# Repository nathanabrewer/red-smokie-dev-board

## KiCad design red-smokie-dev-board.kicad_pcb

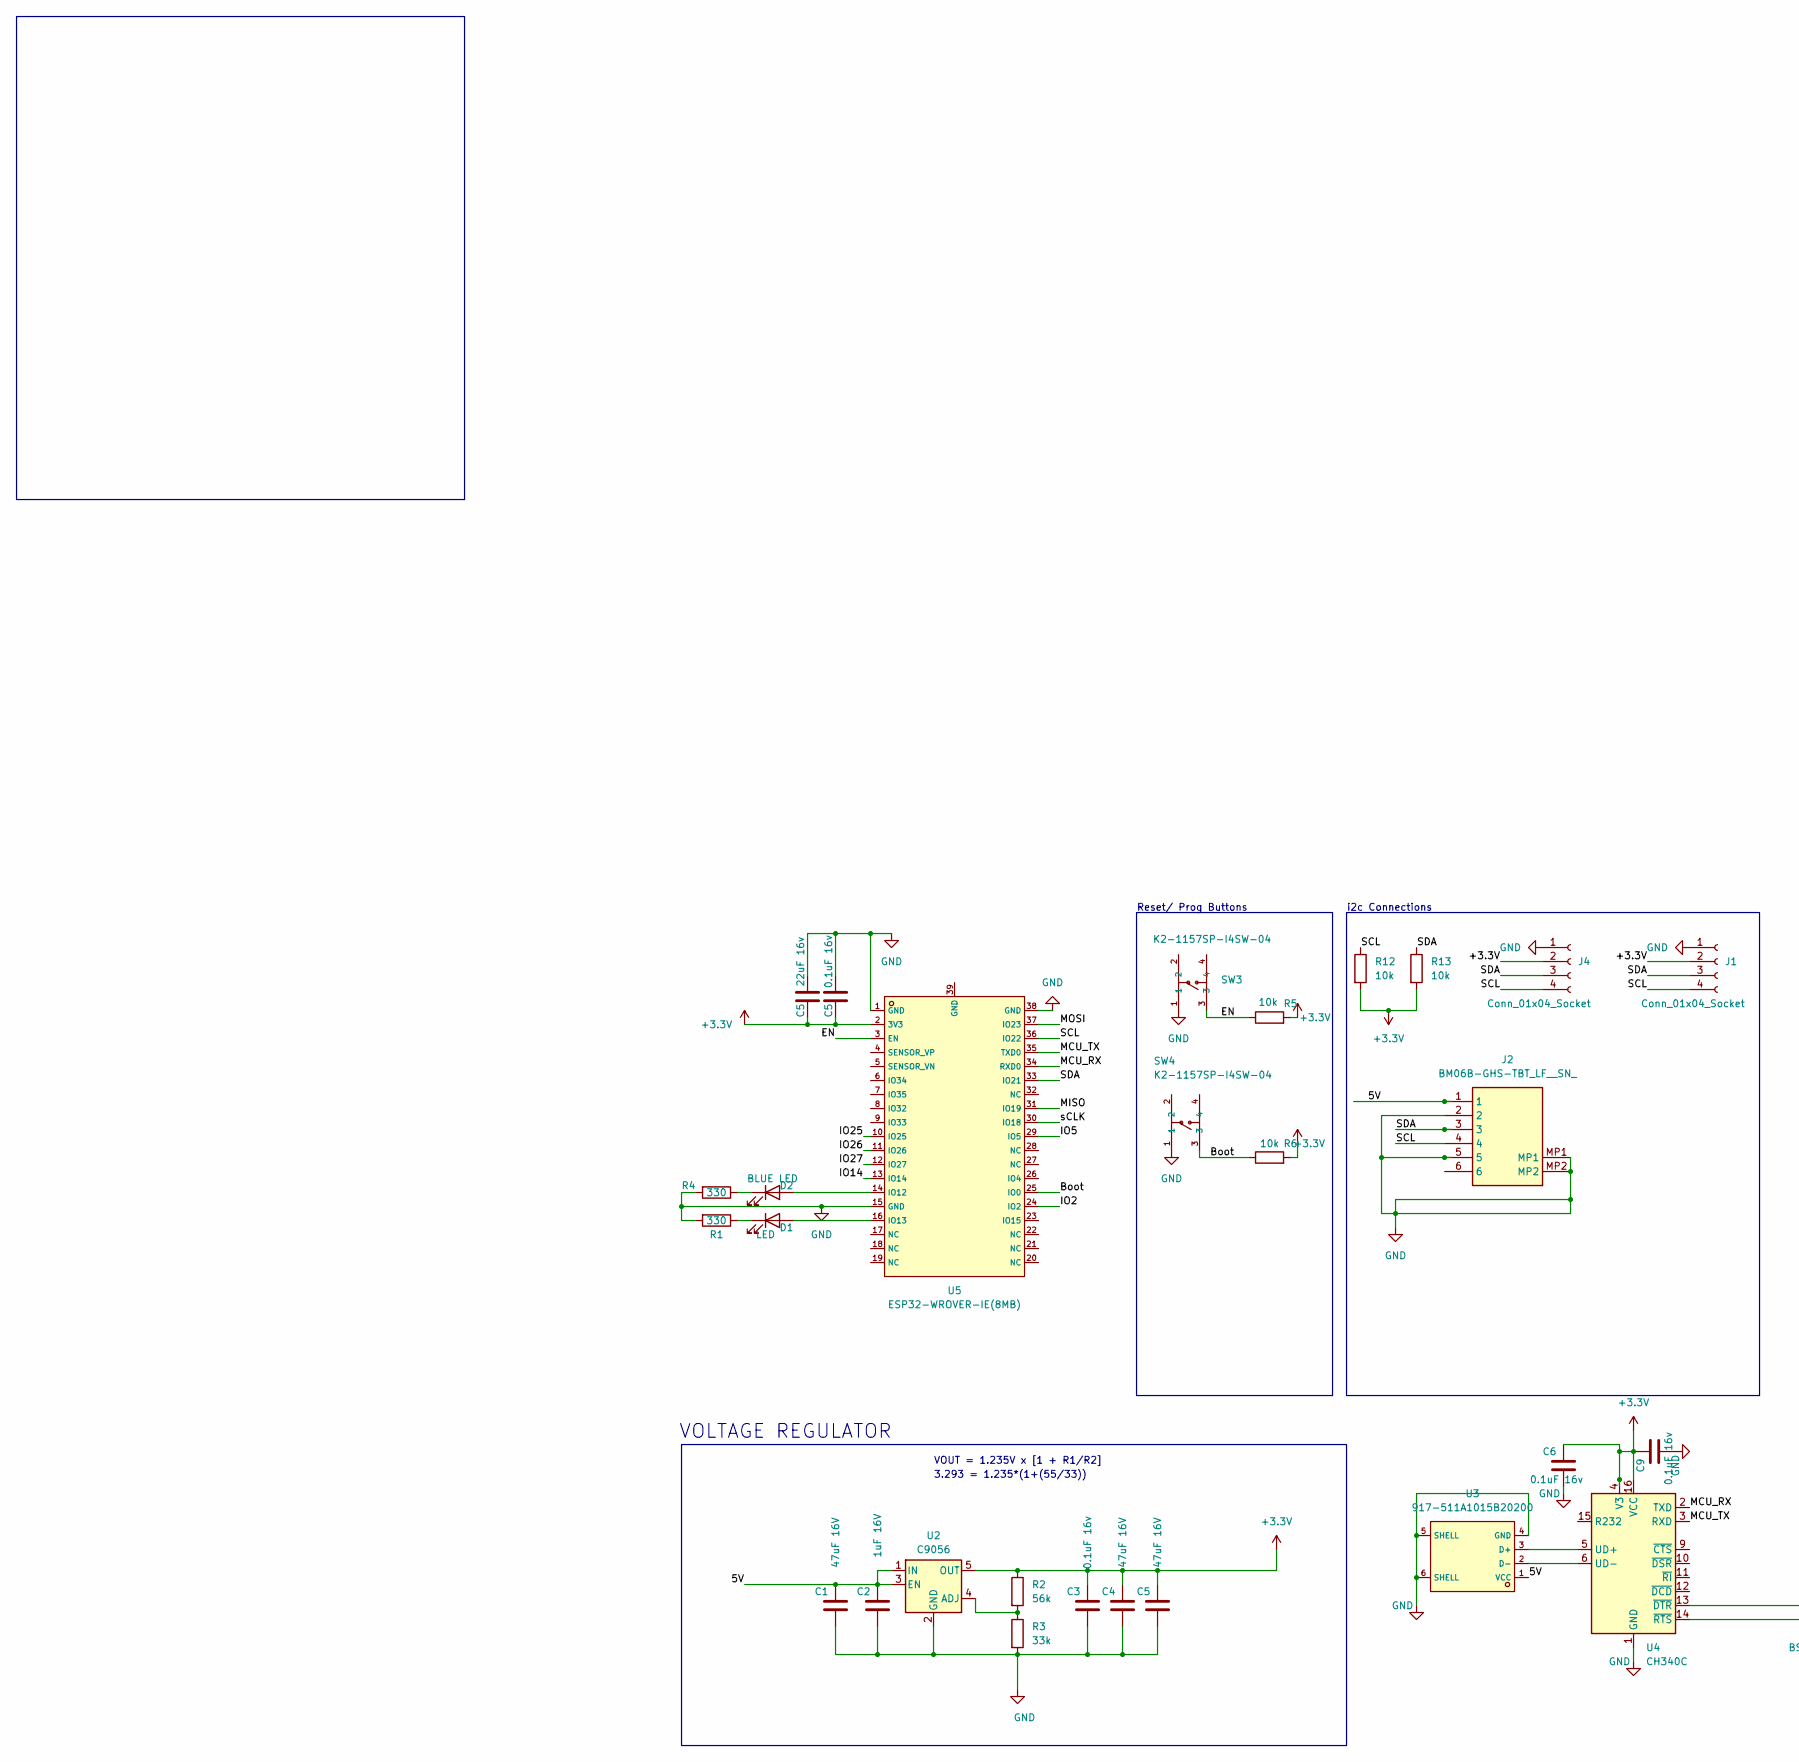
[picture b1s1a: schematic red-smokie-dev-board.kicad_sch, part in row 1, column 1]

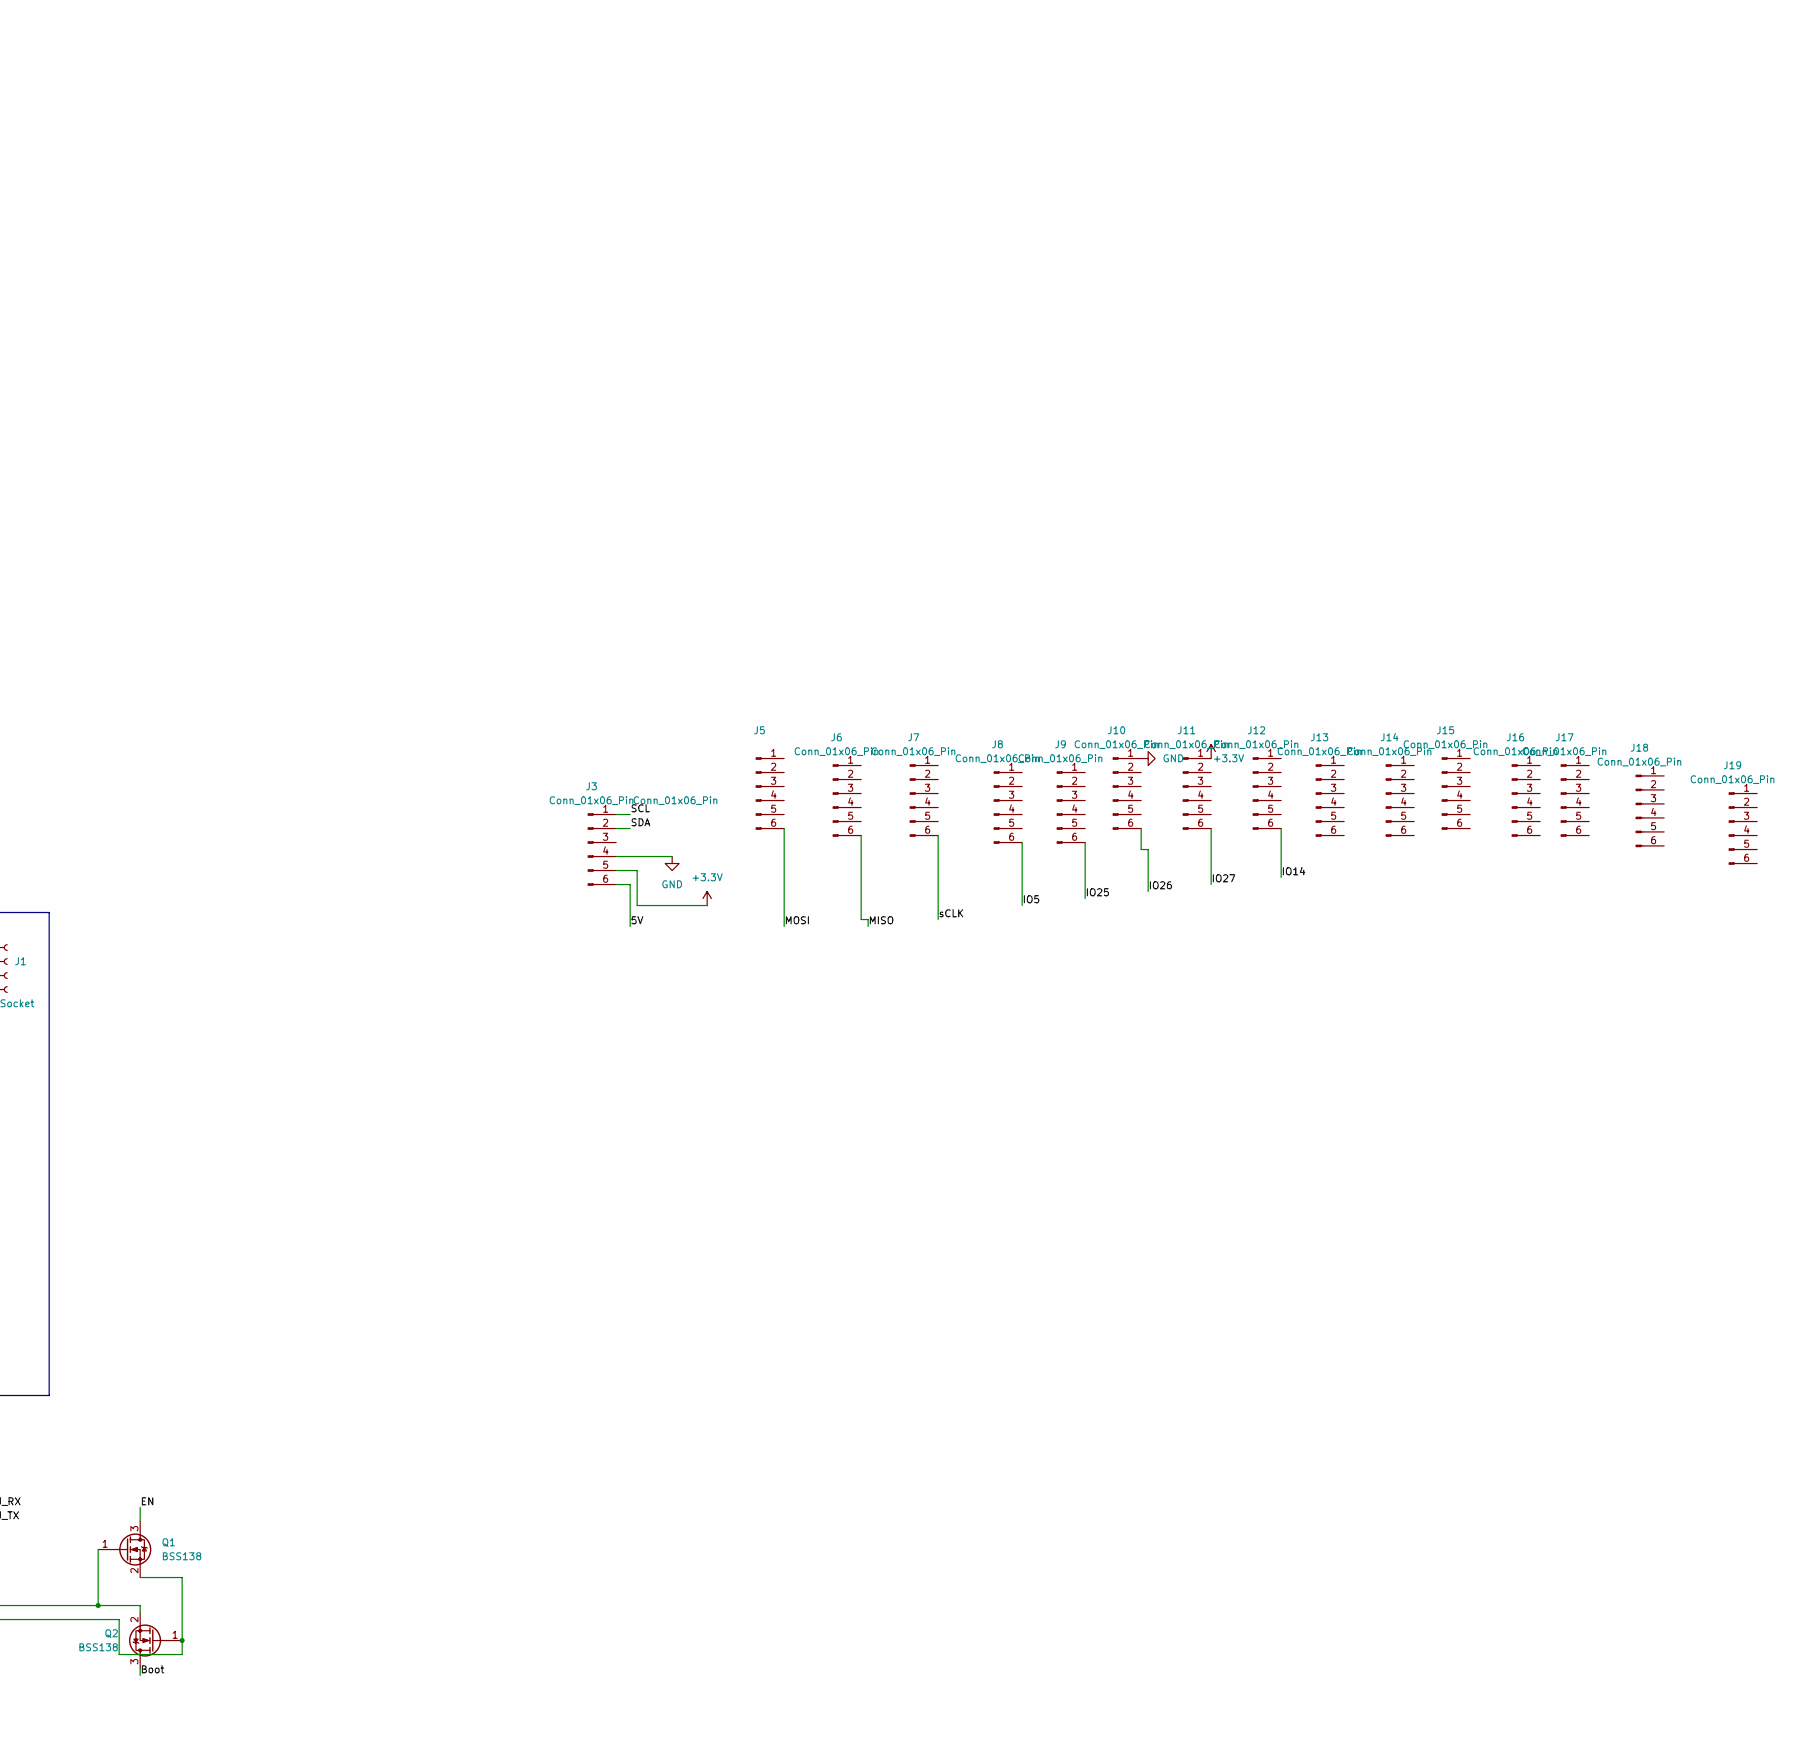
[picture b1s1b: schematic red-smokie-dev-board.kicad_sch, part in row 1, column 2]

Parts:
C1, C4, C5: 47uF 16V; C_0805_2012Metric; mpn C2012X5R1A476M125AC
C2: 1uF 16V; C_0805_2012Metric
C3, C6, C9: 0.1uF 16v; C_0603_1608Metric; mpn CC0603KRX7R7BB104
D1: LED; LED_0603_1608Metric; MPN C2286
D2: BLUE LED; LED_0603_1608Metric; MPN C264465
J1, J4: Conn_01x04_Socket; JST_SH_BM04B-SRSS-TB_1x04-1MP_P1.00mm_Vertical
J2: BM06B-GHS-TBT_LF__SN_; BM06BGHSTBTLFSN; Manufacturer_Part_Number BM06B-GHS-TBT(LF)(SN)
J3, J5, J6, J7, J8, J9, J10, J11, J12, J13, J14, J15, J16, J17, J18, J19: Conn_01x06_Pin; PinSocket_1x06_P2.54mm_Vertical_ALT
Q1, Q2: BSS138; SOT-23
R1, R4: 330; R_0603_1608Metric
R2: 56k; R_0603_1608Metric
R3: 33k; R_0603_1608Metric
R5, R6: 10k; R_0603_1608Metric
R12, R13: 10k; R_0603_1608Metric_Pad0.98x0.95mm_HandSolder
SW3, SW4: K2-1157SP-I4SW-04; SW-SMD_4P-L6.2-W6.2-P4.50-LS8.6; LCSC C2909692
U2: C9056; SOT-23-5
U3: 917-511A1015B20200; USB-A-TH_917-511A1015B20200; LCSC C2763393
U4: CH340C; SOIC-16_3.9x9.9mm_P1.27mm
U5: ESP32-WROVER-IE(8MB); WIFI-SMD_ESP32-WROVER-E; LCSC C701351

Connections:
+3.3V: C3.2, C4.2, C5.2, C6.2, C9.2, J1.2, J3.5, J4.2, J11.1, R2.1, R5.2, R6.2, R12.2, R13.2, U2.5 (OUT), U4.4 (V3), U4.16 (VCC), U5.2 (3V3); also elsewhere on the board
/5V: C1.2, C2.2, J2.1, J3.6, U2.1 (IN), U2.3 (EN), U3.1 (VCC)
/Boot: Q2.3 (D), R6.1, SW4.3, U5.25 (IO0)
/EN: Q1.3 (D), R5.1, SW3.3, U5.3 (EN)
/IO2: U5.24 (IO2)
/IO5: J8.6, U5.29 (IO5)
/IO14: J12.6, U5.13 (IO14)
/IO25: J9.6, U5.10 (IO25)
/IO26: J10.6, U5.11 (IO26)
/IO27: J11.6, U5.12 (IO27)
/MCU_RX: U4.2 (TXD), U5.34 (RXD0)
/MCU_TX: U4.3 (RXD), U5.35 (TXD0)
/MISO: J6.6, U5.31 (IO19)
/MOSI: J5.6, U5.37 (IO23)
/SCL: J1.4, J2.4, J3.1, J4.4, R12.1, U5.36 (IO22)
/SDA: J1.3, J2.3, J3.2, J4.3, R13.1, U5.33 (IO21)
/sCLK: J7.6, U5.30 (IO18)
GND: C1.1, C2.1, C3.1, C4.1, C5.1, C6.1, C9.1, J1.1, J2.2, J2.5, J2.MP1, J2.MP2, J3.4, J4.1, J10.1, R1.2, R3.2, R4.2, SW3.1, SW4.1, U2.2 (GND), U3.4 (GND), U3.5 (SHELL), U3.6 (SHELL), U4.1 (GND), U5.1 (GND), U5.15 (GND), U5.38 (GND); also elsewhere on the board
unnamed: D1.2 (A), U5.16 (IO13)
unnamed: D1.1 (K), R1.1
unnamed: D2.2 (A), U5.14 (IO12)
unnamed: D2.1 (K), R4.1
unnamed: Q1.1 (G), Q2.2 (S), U4.13 (~DTR)
unnamed: Q1.2 (S), Q2.1 (G), U4.14 (~RTS)
unnamed: R2.2, R3.1, U2.4 (ADJ)
unnamed: U3.3 (D+), U4.5 (UD+)
unnamed: U3.2 (D-), U4.6 (UD-)

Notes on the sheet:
3.293 = 1.235*(1+(55/33))
VOUT = 1.235V x [1 + R1/R2]
i2c Connections
VOLTAGE REGULATOR
Reset/ Prog Buttons

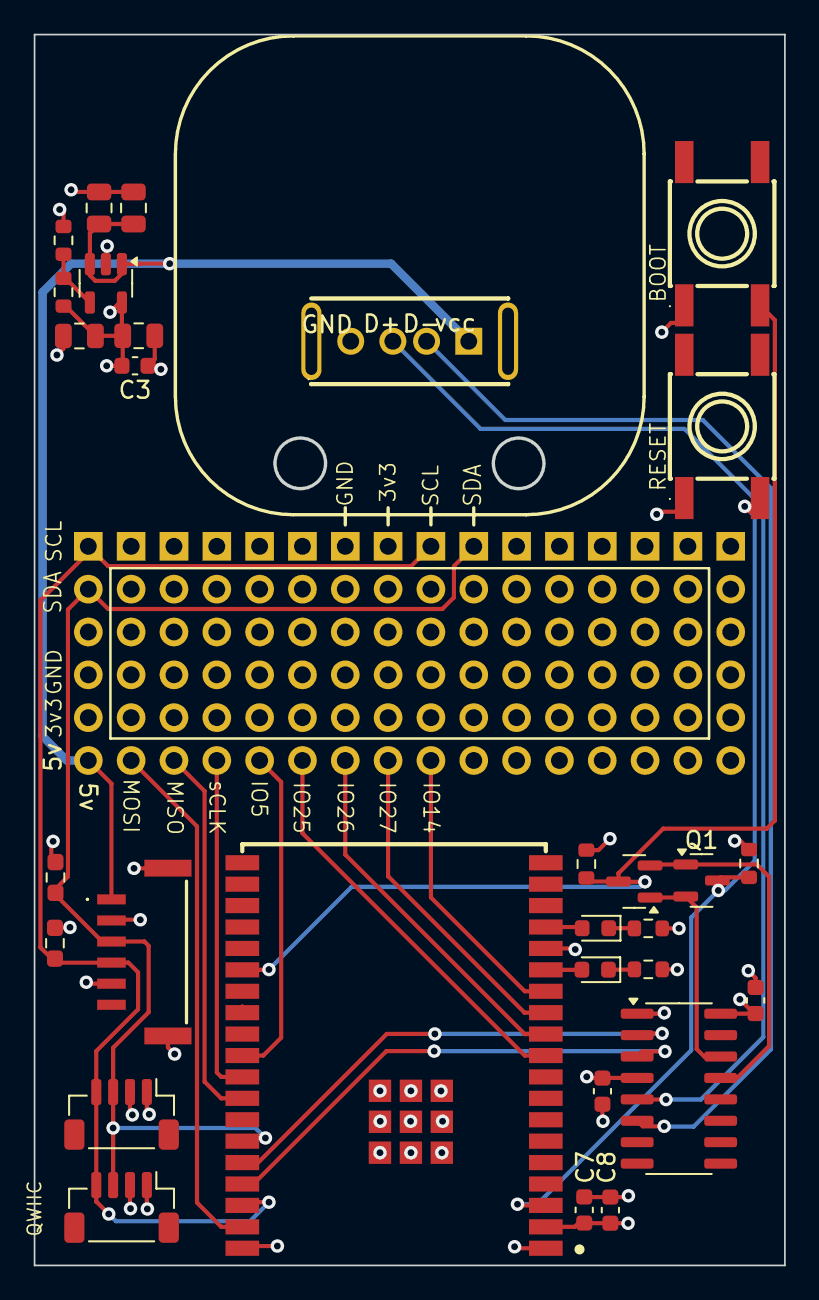
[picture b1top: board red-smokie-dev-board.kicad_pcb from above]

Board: 4 copper layers, 44.4 x 72.9 mm, 46 parts (0 on the bottom side), 26 nets.

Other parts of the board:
C7: 0.1uF 16v; C_0603_1608Metric
C8: 22uF 16v; C_0603_1608Metric

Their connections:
+3.3V: C7.2, C8.2; also elsewhere on the board
GND: C7.1, C8.1; also elsewhere on the board
